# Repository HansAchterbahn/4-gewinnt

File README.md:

# 4 Gewinnt mit LED Matrix und Raspberry Pi

Das hier liegende Projekt ist ein 4 Gewinnt Spiel. Es funktioniert mit Raspberry Pi und einer LED Matrix. Eine genaue Beschreibung des Projekts findet ihr in dem Ordner *Dokumentaton* oder auf meinem Blog. 
Viel Spaß beim ausprobieren und erweitern!  

Blog:  
https://aetzenloetenprogrammieren.blogspot.de/2016/06/4-gewinnt-auf-led-matrix-mit-raspberry.html

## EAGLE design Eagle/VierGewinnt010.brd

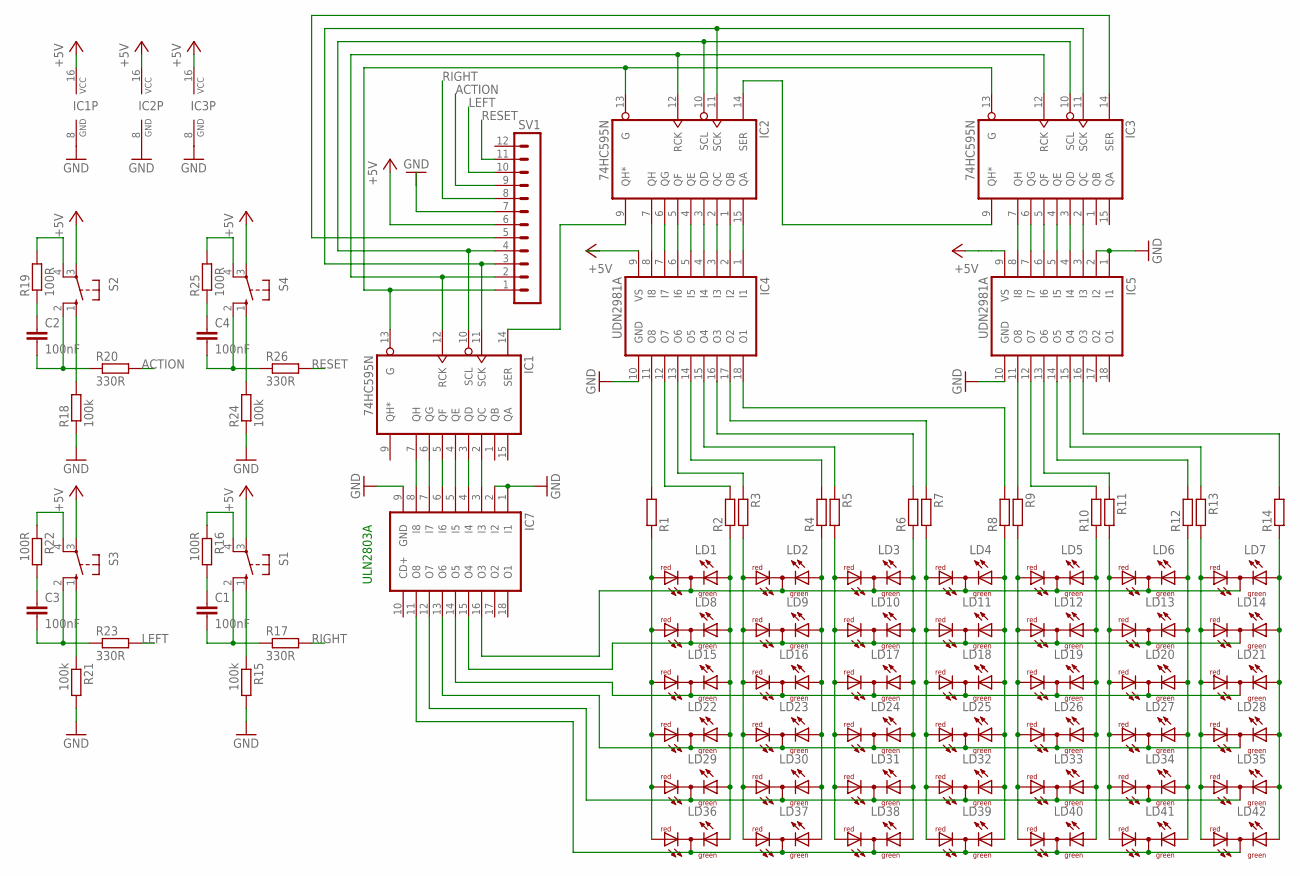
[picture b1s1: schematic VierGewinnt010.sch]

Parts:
C1, C2, C3, C4: 100nF; C0805
IC1, IC2, IC3: 74HC595N; DIL16
IC4, IC5: UDN2981A; DIL18
IC7: ULN2803A; DIL18
LD1, LD2, LD3, LD4, LD5, LD6, LD7, LD8, LD9, LD10, LD11, LD12, LD13, LD14, LD15, LD16, LD17, LD18, LD19, LD20, LD21, LD22, LD23, LD24, LD25, LD26, LD27, LD28, LD29, LD30, LD31, LD32, LD33, LD34, LD35, LD36, LD37, LD38, LD39, LD40, LD41, LD42: DUOLED-RG-C; DUOLED-C-5MM
R1, R2, R3, R4, R5, R6, R7, R8, R9, R10, R11, R12, R13, R14: R-EU_0207/10; 0207/10
R15, R18, R21, R24: 100k; R0603
R16, R19, R22, R25: 100R; R0603
R17, R20, R23, R26: 330R; R0603
S1, S2, S3, S4: 10-XX; B3F-10XX
SV1: MA12-1

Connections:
+5V: IC1.16 (VCC), IC2.16 (VCC), IC3.16 (VCC), IC4.9 (VS), IC5.9 (VS), S1.3, S2.3, S3.3, S4.3, SV1.6
ACTION: R20.2, SV1.9
GND: IC1.8 (GND), IC2.8 (GND), IC3.8 (GND), IC4.10 (GND), IC5.1 (I1), IC5.2 (I2), IC5.10 (GND), IC7.1 (I1), IC7.2 (I2), IC7.9 (GND), R15.2, R18.1, R21.2, R24.1, SV1.7
LEFT: R23.2, SV1.10
unnamed: LD1.AR, LD8.AR, LD15.AR, LD22.AR, LD29.AR, LD36.AR, R1.1
unnamed: LD1.AX (AG), LD8.AX (AG), LD15.AX (AG), LD22.AX (AG), LD29.AX (AG), LD36.AX (AG), R2.1
unnamed: LD2.AR, LD9.AR, LD16.AR, LD23.AR, LD30.AR, LD37.AR, R3.2
unnamed: LD2.AX (AG), LD9.AX (AG), LD16.AX (AG), LD23.AX (AG), LD30.AX (AG), LD37.AX (AG), R4.1
unnamed: LD3.AR, LD10.AR, LD17.AR, LD24.AR, LD31.AR, LD38.AR, R5.2
unnamed: LD3.AX (AG), LD10.AX (AG), LD17.AX (AG), LD24.AX (AG), LD31.AX (AG), LD38.AX (AG), R6.1
unnamed: LD4.AR, LD11.AR, LD18.AR, LD25.AR, LD32.AR, LD39.AR, R7.2
unnamed: LD4.AX (AG), LD11.AX (AG), LD18.AX (AG), LD25.AX (AG), LD32.AX (AG), LD39.AX (AG), R8.1
unnamed: LD5.AR, LD12.AR, LD19.AR, LD26.AR, LD33.AR, LD40.AR, R9.2
unnamed: LD5.AX (AG), LD12.AX (AG), LD19.AX (AG), LD26.AX (AG), LD33.AX (AG), LD40.AX (AG), R10.1
unnamed: LD6.AR, LD13.AR, LD20.AR, LD27.AR, LD34.AR, LD41.AR, R11.2
unnamed: LD6.AX (AG), LD13.AX (AG), LD20.AX (AG), LD27.AX (AG), LD34.AX (AG), LD41.AX (AG), R12.1
unnamed: LD7.AR, LD14.AR, LD21.AR, LD28.AR, LD35.AR, LD42.AR, R13.2
unnamed: LD7.AX (AG), LD14.AX (AG), LD21.AX (AG), LD28.AX (AG), LD35.AX (AG), LD42.AX (AG), R14.1
unnamed: IC7.16 (O3), LD1.C, LD2.C, LD3.C, LD4.C, LD5.C, LD6.C, LD7.C
unnamed: IC7.14 (O5), LD15.C, LD16.C, LD17.C, LD18.C, LD19.C, LD20.C, LD21.C
unnamed: IC7.13 (O6), LD22.C, LD23.C, LD24.C, LD25.C, LD26.C, LD27.C, LD28.C
unnamed: IC7.12 (O7), LD29.C, LD30.C, LD31.C, LD32.C, LD33.C, LD34.C, LD35.C
unnamed: IC7.11 (O8), LD36.C, LD37.C, LD38.C, LD39.C, LD40.C, LD41.C, LD42.C
unnamed: IC4.11 (O8), R1.2
unnamed: IC4.12 (O7), R2.2
unnamed: IC4.13 (O6), R3.1
unnamed: IC4.14 (O5), R4.2
unnamed: IC4.15 (O4), R5.1
unnamed: IC4.16 (O3), R6.2
unnamed: IC4.17 (O2), R7.1
unnamed: IC4.18 (O1), R8.2
unnamed: IC5.11 (O8), R9.1
unnamed: IC5.12 (O7), R10.2
unnamed: IC5.13 (O6), R11.1
unnamed: IC5.14 (O5), R12.2
unnamed: IC5.15 (O4), R13.1
unnamed: IC5.16 (O3), R14.2
unnamed: IC2.1 (QB), IC4.2 (I2)
unnamed: IC2.2 (QC), IC4.3 (I3)
unnamed: IC2.3 (QD), IC4.4 (I4)
unnamed: IC2.4 (QE), IC4.5 (I5)
unnamed: IC2.5 (QF), IC4.6 (I6)
unnamed: IC2.6 (QG), IC4.7 (I7)
unnamed: IC2.7 (QH), IC4.8 (I8)
unnamed: IC2.15 (QA), IC4.1 (I1)
unnamed: R22.1, S3.4 (P1)
unnamed: IC3.2 (QC), IC5.3 (I3)
unnamed: IC3.3 (QD), IC5.4 (I4)
unnamed: IC3.4 (QE), IC5.5 (I5)
unnamed: IC3.5 (QF), IC5.6 (I6)
unnamed: IC3.6 (QG), IC5.7 (I7)
unnamed: IC3.7 (QH), IC5.8 (I8)
unnamed: C1.1, R16.2
unnamed: IC2.14 (SER), IC3.9 (QH*)
unnamed: IC1.14 (SER), IC2.9 (QH*)
unnamed: IC1.13 (G), IC2.13 (G), IC3.13 (G), SV1.1
unnamed: IC1.12 (RCK), IC2.12 (RCK), IC3.12 (RCK), SV1.2
unnamed: IC1.10 (SCL), IC2.10 (SCL), IC3.10 (SCL), SV1.4
unnamed: IC1.11 (SCK), IC2.11 (SCK), IC3.11 (SCK), SV1.3
unnamed: IC3.14 (SER), SV1.5
unnamed: R18.2, S2.1 (S)
unnamed: R19.2, S2.4 (P1)
unnamed: C1.2, R17.1, S1.2 (S1)
unnamed: R16.1, S1.4 (P1)
unnamed: C3.2, R23.1, S3.2 (S1)
unnamed: C2.2, R20.1, S2.2 (S1)
unnamed: R21.1, S3.1 (S)
unnamed: R15.1, S1.1 (S)
unnamed: C4.1, R25.1
unnamed: R25.2, S4.4 (P1)
unnamed: C2.1, R19.1
unnamed: C4.2, R26.1, S4.2 (S1)
unnamed: C3.1, R22.2
unnamed: R24.2, S4.1 (S)
unnamed: IC1.2 (QC), IC7.3 (I3)
unnamed: IC1.3 (QD), IC7.4 (I4)
unnamed: IC1.4 (QE), IC7.5 (I5)
unnamed: IC1.5 (QF), IC7.6 (I6)
unnamed: IC1.6 (QG), IC7.7 (I7)
unnamed: IC1.7 (QH), IC7.8 (I8)
unnamed: IC7.15 (O4), LD8.C, LD9.C, LD10.C, LD11.C, LD12.C, LD13.C, LD14.C
RESET: R26.2, SV1.11
RIGHT: R17.2, SV1.8

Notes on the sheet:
ULN2803A

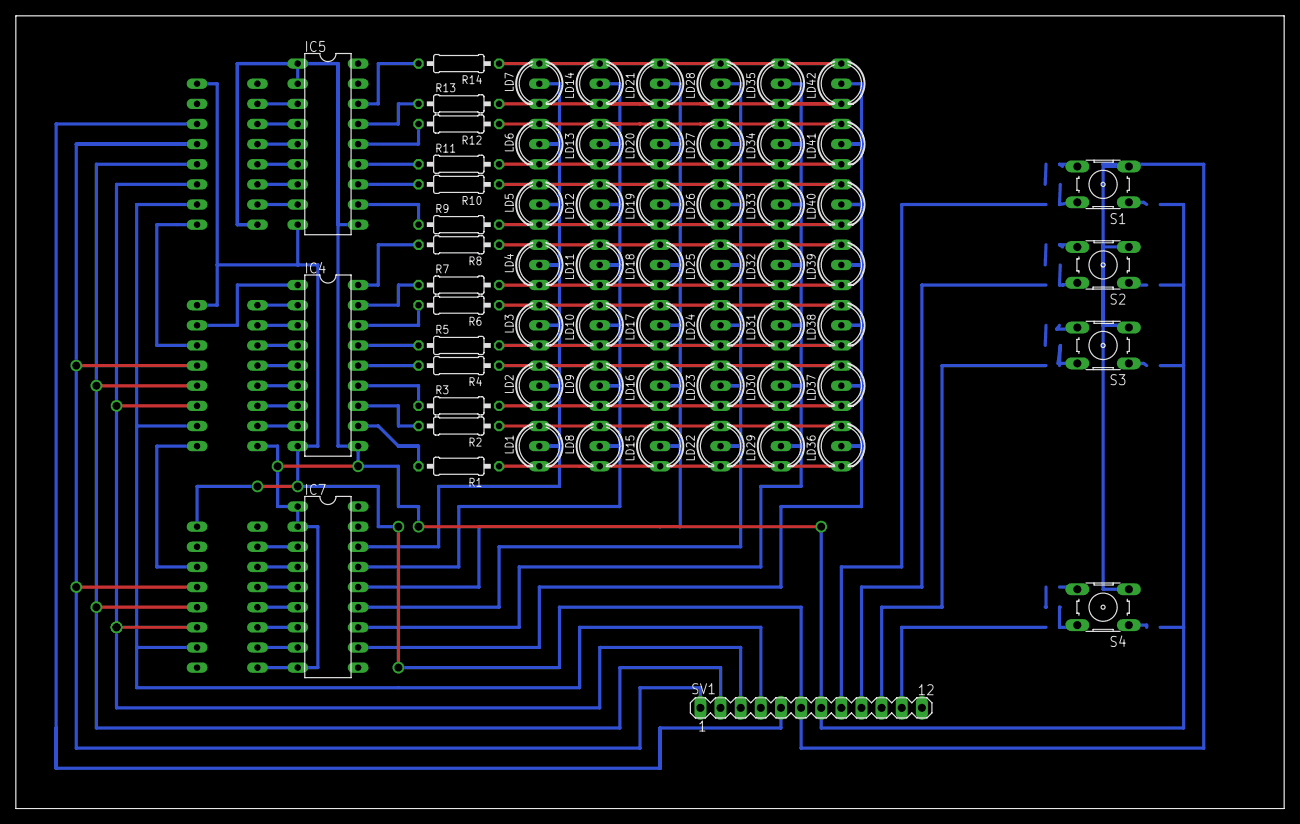
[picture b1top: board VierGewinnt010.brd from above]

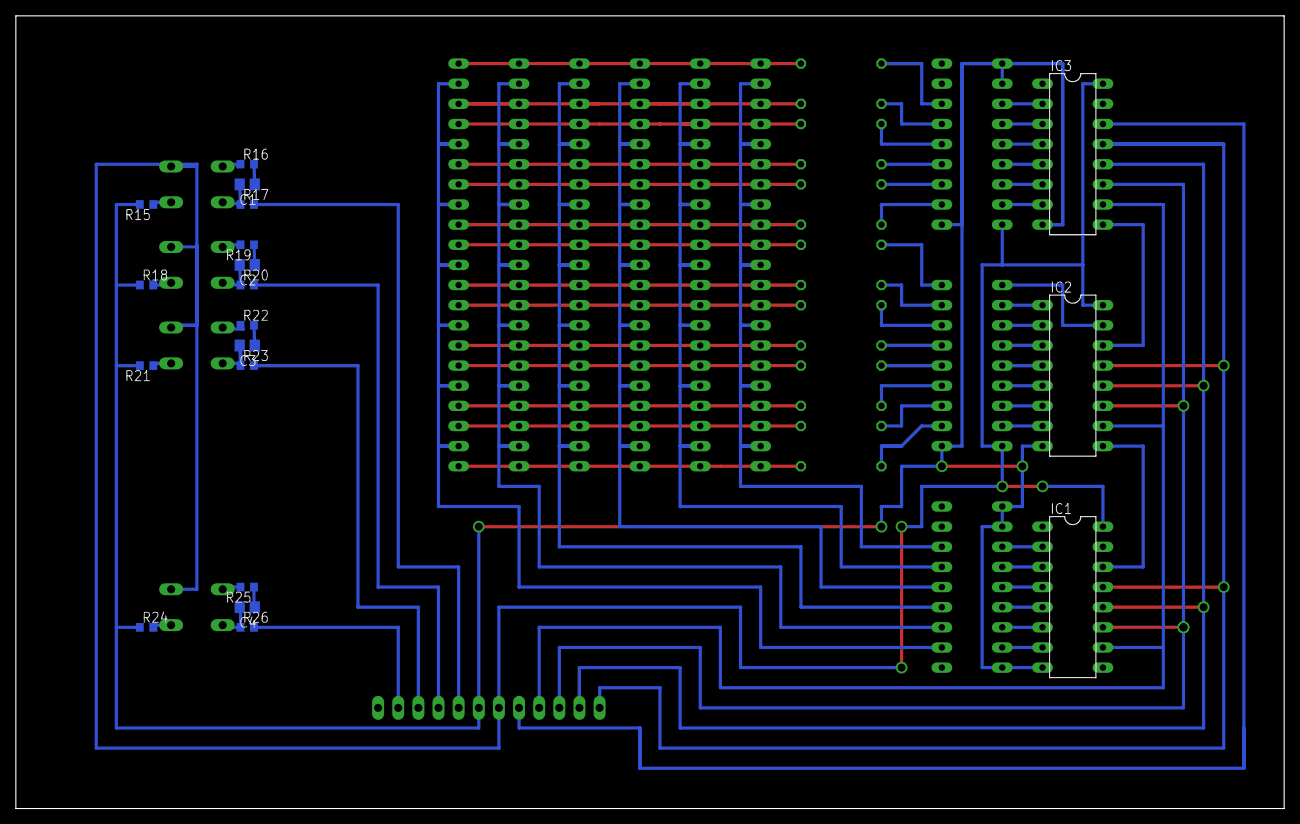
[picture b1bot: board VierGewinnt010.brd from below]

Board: 2 copper layers, 160.0 x 100.0 mm, 83 parts (19 on the bottom side), 83 nets.

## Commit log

2017-01-16 Datenblätter hinzugefügt Dokumentation hinzugefügt Eagle CAD Daten hinzugefügt Python Programmcode hinzugefügt How To Video hinzugefügt
